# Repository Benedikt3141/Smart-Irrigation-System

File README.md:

→ AI Preview

# Smart Irrigation System

The Smart Irrigation System is a battery-powered monitoring and control system for watering up to six individual plants.
Each plant is monitored by a capacitive soil moisture sensor connected to the main control unit.

The project currently focuses on the main monitoring and control unit. A separate watering unit is planned but not fully designed yet. Communication between both units is intended to use ESP-NOW.

## Project Overview

The system consists of two main parts:

### Main Monitoring and Control Unit

The main unit collects sensor data, displays current measurements on a TFT screen, logs data to an SD card and indicates the system status using an LED strip.

Each soil moisture sensor is connected individually using an audio jack connector.

### Watering Unit

The watering unit is planned as a separate module. It will receive commands from the main control unit via ESP-NOW and control the water flow using a solenoid valve.
The unit should also monitor the water tank level using an ultrasonic sensor.

This part of the system is still work in progress.

## Feature overview

###### Sensors (Inputs)

- **Soil mositure monitoring** for individual plants
- **Temperature**
- Humidity
- Air pressure
- Air Quality
- CO2 concentration
- Solar intensity
- 4 Buttons
- *Tank fill state sensor*

###### Other features and outputs

- **Battery powered**
- 2.4" TFT LCD Screen with resistive touch
- SD log with data saved as .csv
- LED-Strip status indicator
- magnetic valve for watering Control
- *web interface*
- *Push Emails when water is empty/error etc.*

## Repository Structure

This repository contains both the firmware and the PCB design files.

- `/firmware/` contains the PlatformIO firmware project.
- `/firmware/src/` contains the ESP32 source code.
- `/src/pcb/` contains the KiCad PCB design files.
- `/src/pcb/gerbers/` contains the exported Gerber files for manufacturing.

## File Structure

```
Smart-Irrigation-System/
├── firmware/
├── images/
├── src/│  
│   ├── assembly_and_models/
│   │   ├── SmartIrrigationSystem-Assembly.step
│   │   └── SmartIrrigationSystem.FCStd
│   └── pcb/
│       └── Smart_Irrigation_SytemV2/
├── .gitignore
├── BOM.csv
├── Concept.jpg
├── JOURNAL.md
├── LICENSE
├── README.md
├── cart_adafruit.png
└── cart_jlcpcb.png

```

## Getting started

#### Requirements

To work with this project, you need:

* VS Code
* PlatformIO or pioarduino IDE Extension
* C++ Compiler
* KiCad 10.0.1 or later

#### Installation

Use git to clone this repository into your computer.

```
git clone https://github.com/Benedikt3141/Smart-Irrigation-System.git
```

Open the project folder in VS Code and build/upload the firmware using PlatformIO or pioarduino.

###### Hardware

You can either use the provided Gerber files or modify the KiCad project and generate new manufacturing files for your preferred PCB supplier.

You can find the gerberfiles [here ](src/pcb/Smart_Irrigation_SystemV2/production). The correlating `BOM.csv` and `position.csv` can be found in the same directories.

## License

[MIT](https://choosealicense.com/licenses/mit/)

## Current Project Status

This project is still in development.

The main monitoring unit is mostly implemented. The watering unit, web interface and notification system are planned but not finished yet.

## Sources

[MQ2 Library](https://github.com/labay11/MQ-2-sensor-library/)
[SD Card](https://RandomNerdTutorials.com/esp32-web-server-microsd-card/)

## AI Usage

Most of the code was written by myself. Since this is a work in progress, the code may still contain bugs or parts that could be improved.

I used AI for debugging assistance, spelling correction, research and for generating the concept visualization shown at the top of this README.

The visualization is intended only as a preview of the planned device and
does not represent the final manufactured hardware.

The PCB design, hardware architecture and most of the firmware were
created by myself.

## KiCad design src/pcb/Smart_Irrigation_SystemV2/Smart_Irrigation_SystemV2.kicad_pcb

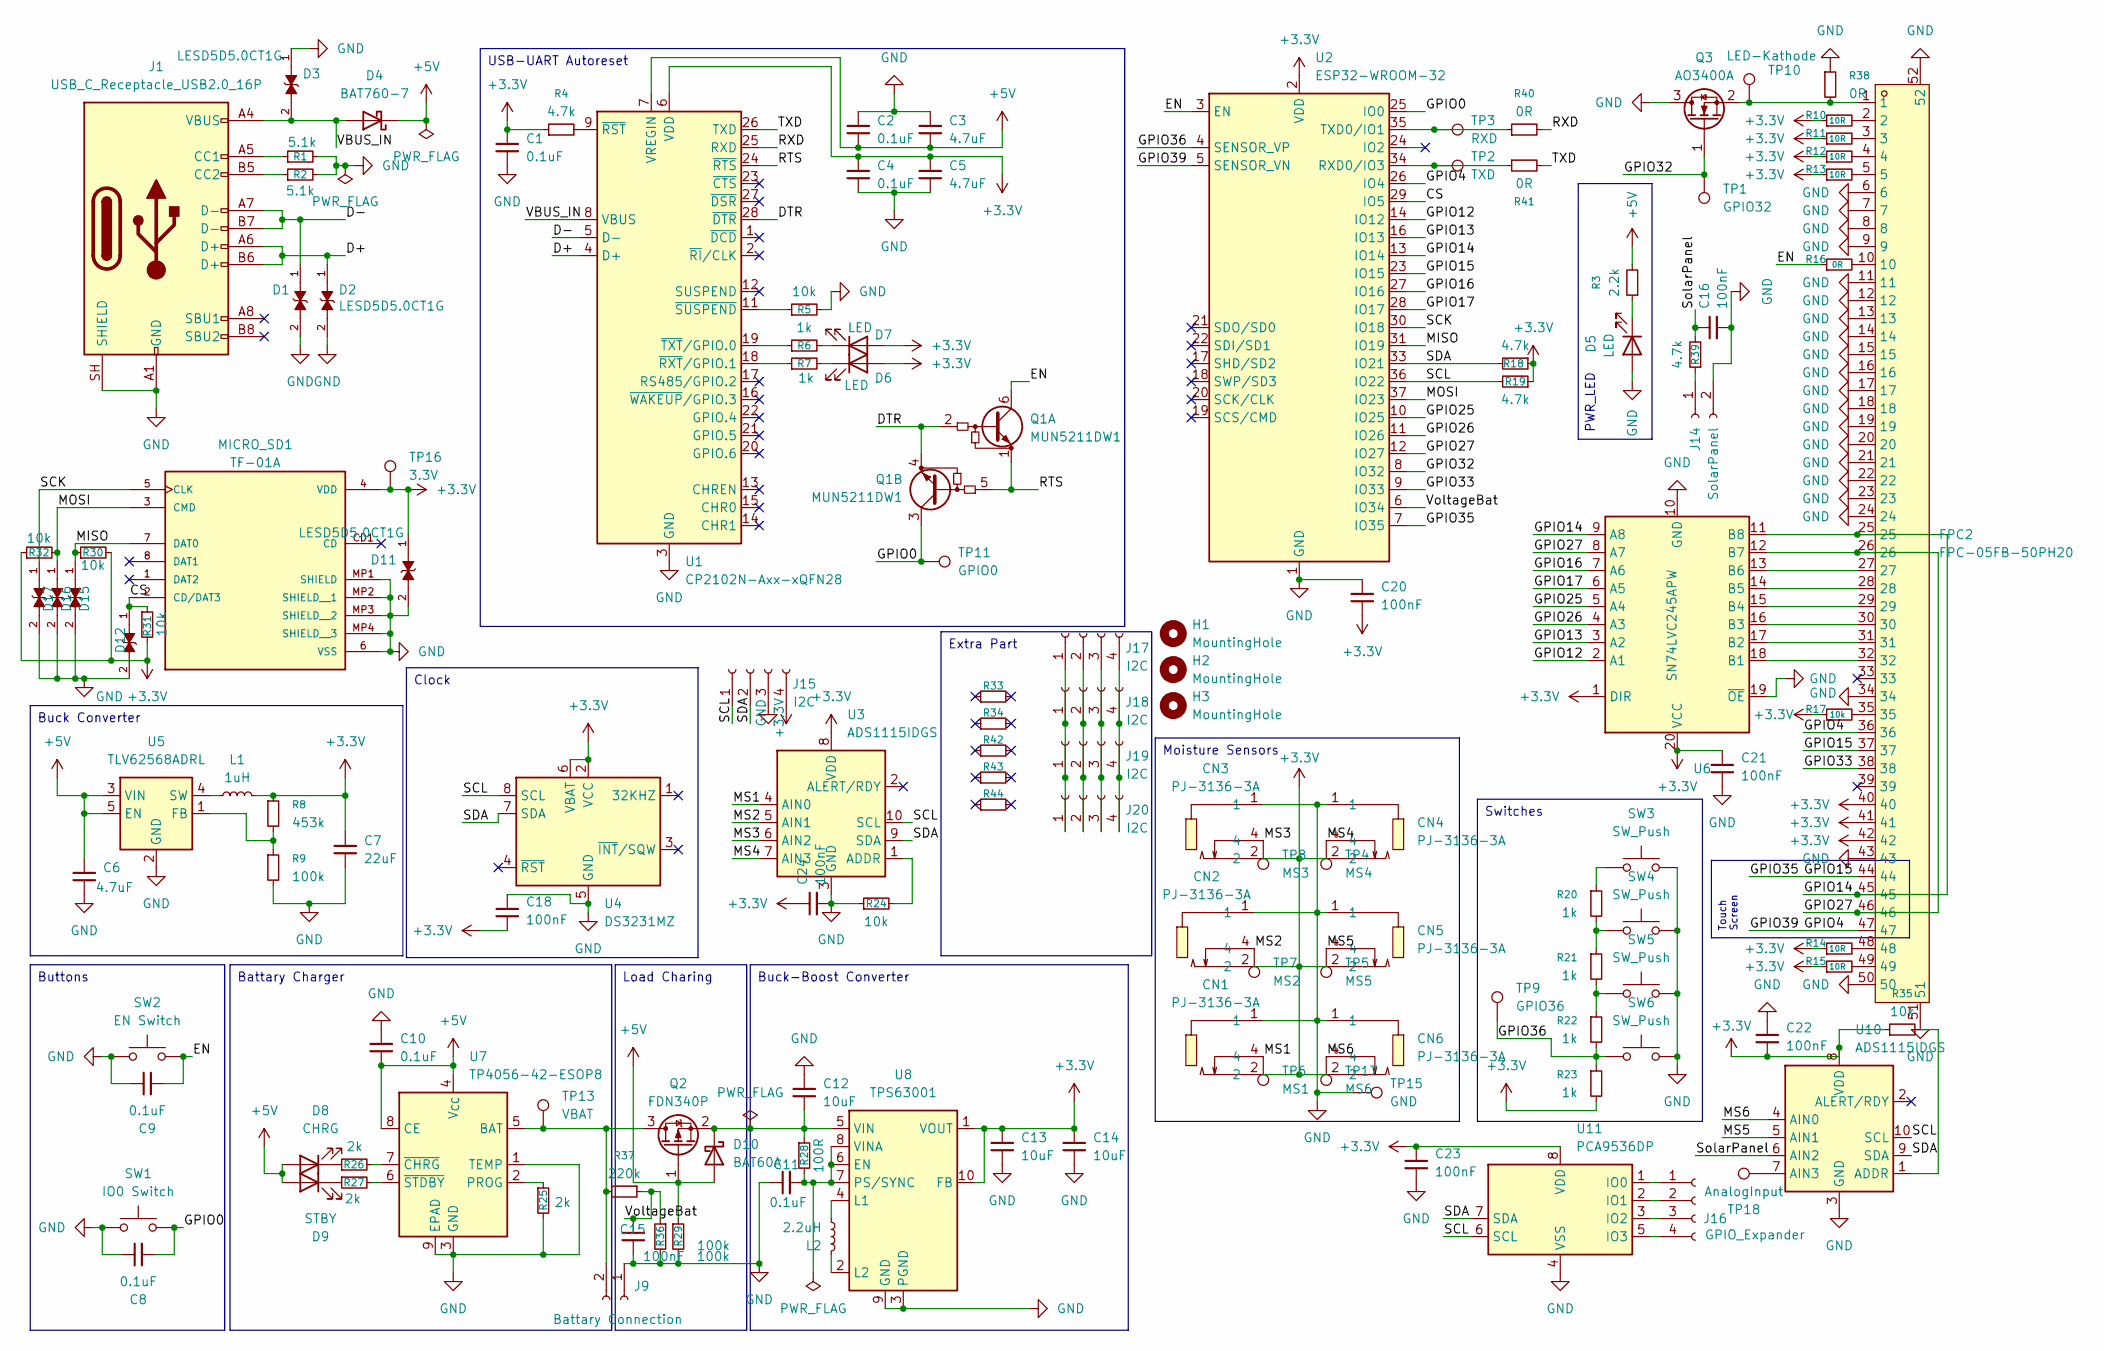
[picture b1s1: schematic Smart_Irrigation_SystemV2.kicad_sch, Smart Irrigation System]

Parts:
C1, C2, C4, C8, C9, C10, C11: 0.1uF; C_0805_2012Metric; JLCPCB Part Number C28233
C3, C5, C6: 4.7uF; C_0805_2012Metric; JLCPCB Part Number C1779
C7: 22uF; C_0805_2012Metric; JLCPCB Part Number C45783
C12, C13, C14: 10uF; C_0805_2012Metric; JLCPCB Part Number C15850
C15, C16, C18, C20, C21, C22, C23, C24: 100nF; C_0805_2012Metric; JLCPCB Part Number C29926
CN1, CN2, CN3, CN4, CN5, CN6: PJ-3136-3A; AUDIO-TH_PJ-3136-3A; MPN PJ-3136-3A; LCSC Part C707248
D1, D2, D3, D11, D12, D15, D16, D17: LESD5D5.0CT1G; TVS_LESD5D5.0CT1G; PARTREV O; JLCPCB Part Number C5274290
D4: BAT760-7; D_SOD-323F; JLCPCB Part Number C27636120
D5, D6, D7: LED; D_0603_1608Metric; JLCPCB Part Number C2286
D8: CHRG; D_0603_1608Metric; JLCPCB Part Number C2287
D9: STBY; D_0603_1608Metric; JLCPCB Part Number C12624
D10: BAT60A; D_SOD-323; JLCPCB Part Number C513277
FPC2: FPC-05FB-50PH20; FPC-SMD_50P-P0.50_FPC-05FB-50PH20; MPN FPC-05FB-50PH20; LCSC Part C2856838
H1, H2, H3: MountingHole; MountingHole_2.2mm_M2
J1: USB_C_Receptacle_USB2.0_16P; USB_C_Receptacle_HCTL_HC-TYPE-C-16P-01A; JLCPCB Part Number C5337088
J9: Battary Connection; JST_PH_B2B-PH-K_1x02_P2.00mm_Vertical
J14: SolarPanel; JST_PH_B2B-PH-K_1x02_P2.00mm_Vertical
J15, J17, J18, J19, J20: I2C; PinSocket_1x04_P2.54mm_Vertical
J16: GPIO_Expander; PinSocket_1x04_P2.54mm_Vertical
L1: 1uH; IND-SMD_L7.1-W6.6; JLCPCB Part Number C726315
L2: 2.2uH; IND-SMD_L6.6-W6.6; JLCPCB Part Number C128686
MICRO_SD1: TF-01A; TF-SMD_TF-01A; JLCPCB Part Number C91145
Q1: MUN5211DW1; SOT-363_SC-70-6; JLCPCB Part Number C152507
Q2: FDN340P; SOT-23; JLCPCB Part Number C347510
Q3: AO3400A; SOT-23; JLCPCB Part Number C20917
R1, R2: 5.1k; R_0805_2012Metric; JLCPCB Part Number C26023
R3: 2.2k; R_0805_2012Metric; JLCPCB Part Number C17520
R4, R18, R19, R39: 4.7k; R_0805_2012Metric; JLCPCB Part Number C17673
R5, R17, R24, R30, R31, R32, R35: 10k; R_0805_2012Metric; JLCPCB Part Number C17414
R6, R7, R20, R21, R22, R23: 1k; R_0805_2012Metric; JLCPCB Part Number C17513
R8: 453k; R_0805_2012Metric; JLCPCB Part Number C17702
R9, R29, R36: 100k; R_0805_2012Metric; JLCPCB Part Number C25611
R10, R11, R12, R13, R14, R15: 10R; R_0805_2012Metric; JLCPCB Part Number C17415
R16: 0R; R_0805_2012Metric; JLCPCB Part Number C17477
R25, R26, R27: 2k; R_0805_2012Metric; JLCPCB Part Number C17604
R28: 100R; R_0805_2012Metric; JLCPCB Part Number C17408
R33: 0201; R_0201_0603Metric
R34: 0402; R_0402_1005Metric
R37: 220k; R_0805_2012Metric; JLCPCB Part Number C17556
R38: 0R; R_0805_2012Metric
R40, R41: 0R; R_1206_3216Metric; JLCPCB Part Number C17888
R42: 0603; R_0603_1608Metric
R43: 0805; R_0805_2012Metric
R44: 1206; R_1206_3216Metric
SW1: IO0 Switch; KEY-SMD_4P-L6.0-W6.0-P3.90-LS9.0; JLCPCB Part Number C83206
SW2: EN Switch; KEY-SMD_4P-L6.0-W6.0-P3.90-LS9.0; JLCPCB Part Number C83206
SW3, SW4, SW5, SW6: SW_Push; SW_PUSH_6mm_H5mm; JLCPCB Part Number C83206
TP1: GPIO32; TestPoint_Pad_D1.5mm
TP2: TXD; TestPoint_Pad_D1.5mm
TP3: RXD; TestPoint_Pad_D1.5mm
TP4: MS4; TestPoint_Pad_D1.5mm
TP5: MS5; TestPoint_Pad_D1.5mm
TP6: MS1; TestPoint_Pad_D1.5mm
TP7: MS2; TestPoint_Pad_D1.5mm
TP8: MS3; TestPoint_Pad_D1.5mm
TP9: GPIO36; TestPoint_Pad_D1.5mm
TP10: LED-Kathode; TestPoint_Pad_D1.5mm
TP11: GPIO0; TestPoint_Pad_D1.5mm
TP13: VBAT; TestPoint_Pad_D1.5mm
TP15: GND; TestPoint_Pad_2.5x2.5mm
TP16: 3.3V; TestPoint_Pad_2.5x2.5mm
TP17: MS6; TestPoint_Pad_D1.5mm
TP18: AnalogInput; TestPoint_Pad_D1.5mm
U1: CP2102N-Axx-xQFN28; QFN-28-1EP_5x5mm_P0.5mm_EP3.35x3.35mm; JLCPCB Part Number C964632
U2: ESP32-WROOM-32; JLCPCB Part Number C701343
U3, U10: ADS1115IDGS; TSSOP-10_3x3mm_P0.5mm; JLCPCB Part Number C37593
U4: DS3231MZ; SOIC-8_3.9x4.9mm_P1.27mm; JLCPCB Part Number C107410
U5: TLV62568ADRL; SOT-23-5; JLCPCB Part Number C87122
U6: SN74LVC245APW; TSSOP-20_4.4x6.5mm_P0.65mm; JLCPCB Part Number C7848
U7: TP4056-42-ESOP8; ESOP-8_L4.9-W3.9-P1.27-LS6.0-BL-EP; JLCPCB Part Number C16581
U8: TPS63001; VSON-10-1EP_3x3mm_P0.5mm_EP1.65x2.4mm_ThermalVias; JLCPCB Part Number C28060
U11: PCA9536DP; TSSOP-8_3x3mm_P0.65mm; JLCPCB Part Number C2649389

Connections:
+3.3V: C1.1, C4.1, C5.1, C7.1, C13.1, C14.1, C18.2, C20.2, C21.1, C22.2, C23.1, C24.1, CN1.2, CN2.2, CN3.2, CN4.2, CN5.2, CN6.2, D6.2 (A), D7.2 (A), D11.1, FPC2.40, FPC2.41, FPC2.42, J15.4, L1.2, MICRO_SD1.4 (VDD), R4.1, R8.1, R10.1, R11.1, R12.1, R13.1, R14.1, R15.1, R17.1, R18.1, R19.1, R23.2, R30.2, R31.2, R32.1, R35.1, TP16.1 (1_1), U1.6 (VDD), U2.2 (VDD), U3.8 (VDD), U4.2 (VCC), U4.6 (VBAT), U6.1 (DIR), U6.20 (VCC), U8.1 (VOUT), U8.10 (FB), U10.8 (VDD), U11.8 (VDD)
+5V: C2.2, C3.2, C6.1, C10.2, D4.1 (K), D8.2 (A), D9.2 (A), D10.2 (A), Q2.1 (G), R3.2, R29.1, U1.7 (VREGIN), U5.3 (VIN), U5.5 (EN), U7.4 (V_{CC}), U7.8 (CE)
/CS: D12.1, MICRO_SD1.2 (CD/DAT3), R31.1, U2.29 (IO5)
/D+: D2.1, J1.A6 (D+), J1.B6 (D+), U1.4 (D+)
/D-: D1.1, J1.A7 (D-), J1.B7 (D-), U1.5 (D-)
/DTR: Q1.2 (B1), Q1.4 (E2), U1.28 (~DTR)
/EN: C9.2, Q1.6 (C1), R16.1, SW2.2, U2.3 (EN)
/GPIO0: C8.2, Q1.3 (C2), SW1.2, TP11.1 (1_1), U2.25 (IO0)
/GPIO12: U2.14 (IO12), U6.2 (A1)
/GPIO13: U2.16 (IO13), U6.3 (A2)
/GPIO14: FPC2.25, FPC2.45, U2.13 (IO14), U6.9 (A8), U6.11 (B8)
/GPIO15: FPC2.37, FPC2.44, U2.7 (IO35), U2.23 (IO15)
/GPIO16: U2.27 (IO16), U6.7 (A6)
/GPIO17: U2.28 (IO17), U6.6 (A5)
/GPIO25: U2.10 (IO25), U6.5 (A4)
/GPIO26: U2.11 (IO26), U6.4 (A3)
/GPIO27: FPC2.26, FPC2.46, U2.12 (IO27), U6.8 (A7), U6.12 (B7)
/GPIO32: Q3.1 (G), TP1.1 (1_1), U2.8 (IO32)
/GPIO33: FPC2.38, U2.9 (IO33)
/GPIO36: R22.2, R23.1, SW6.1, TP9.1 (1_1), U2.4 (SENSOR_VP)
/GPIO39: FPC2.36, FPC2.47, U2.5 (SENSOR_VN), U2.26 (IO4)
/MISO: D15.1, MICRO_SD1.7 (DAT0), R30.1, U2.31 (IO19)
/MOSI: D16.1, MICRO_SD1.3 (CMD), R32.2, U2.37 (IO23)
/MS1: CN1.4, TP6.1 (1_1), U3.4 (AIN0)
/MS2: CN2.4, TP7.1 (1_1), U3.5 (AIN1)
/MS3: CN3.4, TP8.1 (1_1), U3.6 (AIN2)
/MS4: CN4.4, TP4.1 (1_1), U3.7 (AIN3)
/MS5: CN5.4, TP5.1 (1_1), U10.5 (AIN1)
/MS6: CN6.4, TP17.1 (1_1), U10.4 (AIN0)
/RTS: Q1.1 (E1), Q1.5 (B2), U1.24 (~RTS)
/RXD: R40.2, U1.25 (RXD)
/SCK: D17.1, MICRO_SD1.5 (CLK), U2.30 (IO18)
/SCL: J15.1, R19.2, U2.36 (IO22), U3.10 (SCL), U4.8 (SCL), U10.10 (SCL), U11.6 (SCL)
/SDA: J15.2, R18.2, U2.33 (IO21), U3.9 (SDA), U4.7 (SDA), U10.9 (SDA), U11.7 (SDA)
/SolarPanel: C16.1, R39.2, U10.6 (AIN2)
/TXD: R41.2, U1.26 (TXD)
/VBUS_IN: D3.2, D4.2 (A), J1.A4 (VBUS), J1.A9 (VBUS), J1.B4 (VBUS), J1.B9 (VBUS), U1.8 (VBUS)
/VoltageBat: C15.1, R36.1, R37.1, U2.6 (IO34)
GND: C1.2, C2.1, C3.1, C4.2, C5.2, C6.2, C7.2, C8.1, C9.1, C10.1, C11.1, C12.1, C13.2, C14.2, C15.2, C16.2, C18.1, C20.1, C21.2, C22.1, C23.2, C24.2, CN1.1, CN2.1, CN3.1, CN4.1, CN5.1, CN6.1, D1.2, D2.2, D3.1, D5.2 (A), D11.2, D12.2, D15.2, D16.2, D17.2, FPC2.6, FPC2.7, FPC2.8, FPC2.9, FPC2.11, FPC2.12, FPC2.13, FPC2.14, FPC2.15, FPC2.16, FPC2.17, FPC2.18, FPC2.19, FPC2.20, FPC2.21, FPC2.22, FPC2.23, FPC2.24, FPC2.34, FPC2.43, FPC2.50, FPC2.51, FPC2.52, J1.A1 (GND), J1.A12 (GND), J1.B1 (GND), J1.B12 (GND), J1.SH (SHIELD), J9.1, J14.2, J15.3, MICRO_SD1.6 (VSS), MICRO_SD1.MP1 (SHIELD), MICRO_SD1.MP2 (SHIELD__1), MICRO_SD1.MP3 (SHIELD__2), MICRO_SD1.MP4 (SHIELD__3), Q3.3 (D), R1.2, R2.2, R5.2, R9.2, R24.1, R25.2, R29.2, R36.2, R38.1, SW1.1, SW2.1, SW3.2, SW4.2, SW5.2, SW6.2, TP15.1 (1_1), U1.3 (GND), U1.29 (GND), U2.1 (GND), U2.15 (GND), U2.38 (GND), U2.39 (GND), U3.3 (GND), U4.5 (GND), U5.2 (GND), U6.10 (GND), U6.19 (~OE), U7.1 (TEMP), U7.3 (GND), U7.9 (EPAD), U8.3 (PGND), U8.9 (GND), U8.11 (PGND), U10.3 (GND), U11.4 (VSS)
unnamed: D5.1 (K), R3.1
unnamed: D6.1 (K), R7.2
unnamed: D7.1 (K), R6.2
unnamed: D8.1 (K), R26.1
unnamed: D9.1 (K), R27.1
unnamed: C12.2, D10.1 (K), Q2.2 (S), R28.1, U8.5 (VIN)
unnamed: FPC2.2, R10.2
unnamed: FPC2.3, R11.2
unnamed: FPC2.4, R12.2
unnamed: FPC2.5, R13.2
unnamed: FPC2.10, R16.2
unnamed: FPC2.35, R17.2
unnamed: FPC2.48, R14.2
unnamed: FPC2.49, R15.2
unnamed: J1.A5 (CC1), R1.1
unnamed: J1.B5 (CC2), R2.1
unnamed: J9.2, Q2.3 (D), R37.2, TP13.1 (1_1), U7.5 (BAT)
unnamed: J14.1, R39.1
unnamed: J16.1, U11.1 (IO0)
unnamed: J16.2, U11.2 (IO1)
unnamed: J16.3, U11.3 (IO2)
unnamed: J16.4, U11.5 (IO3)
unnamed: J17.1, J18.1, J19.1, J20.1
unnamed: J17.2, J18.2, J19.2, J20.2
unnamed: J17.3, J18.3, J19.3, J20.3
unnamed: J17.4, J18.4, J19.4, J20.4
unnamed: FPC2.1, Q3.2 (S), R38.2, TP10.1 (1_1)
unnamed: R20.1, SW3.1
unnamed: R20.2, R21.1, SW4.1
unnamed: R21.2, R22.1, SW5.1
unnamed: R4.2, U1.9 (~RST)
unnamed: R7.1, U1.18 (~RXT/GPIO.1)
unnamed: R5.1, U1.11 (~SUSPEND)
unnamed: R6.1, U1.19 (~TXT/GPIO.0)
unnamed: R41.1, TP2.1 (1_1), U2.34 (RXD0/IO3)
unnamed: R40.1, TP3.1 (1_1), U2.35 (TXD0/IO1)
unnamed: R24.2, U3.1 (ADDR)
unnamed: R8.2, R9.1, U5.1 (FB)
unnamed: L1.1, U5.4 (SW)
unnamed: FPC2.32, U6.18 (B1)
unnamed: FPC2.31, U6.17 (B2)
unnamed: FPC2.30, U6.16 (B3)
unnamed: FPC2.29, U6.15 (B4)
unnamed: FPC2.28, U6.14 (B5)
unnamed: FPC2.27, U6.13 (B6)
unnamed: R25.1, U7.2 (PROG)
unnamed: R26.2, U7.7 (~CHRG)
unnamed: R27.2, U7.6 (~STDBY)
unnamed: C11.2, R28.2, U8.6 (EN), U8.7 (PS/SYNC), U8.8 (VINA)
unnamed: L2.1, U8.4 (L1)
unnamed: L2.2, U8.2 (L2)
unnamed: R35.2, U10.1 (ADDR)
unnamed: TP18.1 (1_1), U10.7 (AIN3)

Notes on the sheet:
USB-UART Autoreset
Battary Charger
Clock
Buck Converter
PWR_LED
Buck-Boost Converter
Switches
Touch Screen
Buttons
Moisture Sensors
Load Charing
Extra Part

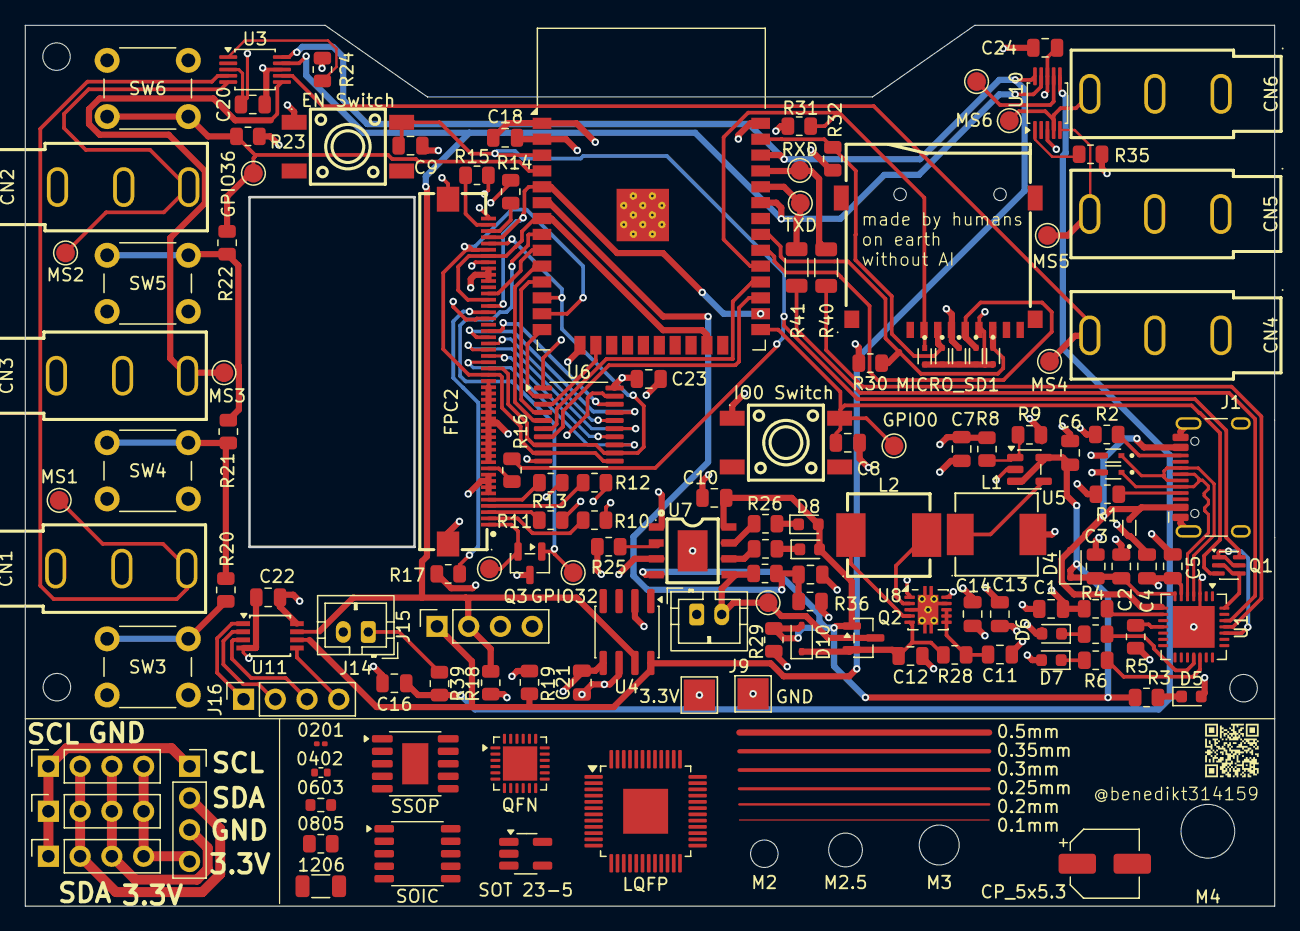
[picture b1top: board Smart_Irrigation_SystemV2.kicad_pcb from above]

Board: 4 copper layers, 100.0 x 70.5 mm, 137 parts (0 on the bottom side), 92 nets.

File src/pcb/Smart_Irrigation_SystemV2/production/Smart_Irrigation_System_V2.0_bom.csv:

Designator,Footprint,Quantity,Value,LCSC Part #
"C1, C10, C11, C2, C4, C8, C9",0805,7,0.1uF,C28233
"C12, C13, C14",0805,3,10uF,C15850
"C15, C16, C17, C18, C20, C21, C22, C23, C24",0805,9,100nF,C29926
"C3, C5, C6",0805,3,4.7uF,C1779
C7,0805,1,22uF,C45783
"CN1, CN2, CN3, CN4, CN5, CN6",AUDIO-TH_PJ-3136-3A,6,PJ-3136-3A,C707248
"D1, D11, D12, D15, D16, D17, D2, D3",TVS_LESD5D5.0CT1G,8,LESD5D5.0CT1G,C5274290
D10,D_SOD-323,1,BAT60A,C5355496
D4,D_SOD-323F,1,BAT760-7,C27636120
"D5, D6, D7",0603,3,LED,C2286
D8,0603,1,CHRG,C2287
D9,0603,1,STBY,C12624
J1,USB_C_Receptacle_HCTL_HC-TYPE-C-16P-01A,1,USB_C_Receptacle_USB2.0_16P,C5337088
"J10, J11, J13, J15, J6",JST_EH_B4B-EH-A_1x04_P2.50mm_Vertical,5,I2C,
J14,JST_PH_B2B-PH-K_1x02_P2.00mm_Vertical,1,SolarPanel,
J16,PinSocket_1x04_P2.54mm_Vertical,1,GPIO_Expander,
J2,CON_5051105091_MOL,1,FPC_Connector,C779387
J9,JST_PH_B2B-PH-K_1x02_P2.00mm_Vertical,1,Battary Connection,
L1,IND-SMD_L7.1-W6.6,1,1uH,C726315
L2,IND-SMD_L6.6-W6.6,1,2.2uH,C128686
MICRO_SD1,TF-SMD_TF-01A,1,TF-01A,C91145
Q1,SOT-363_SC-70-6,1,MUN5211DW1,C152507
Q2,SOT-23,1,FDN340P,C347510
Q3,SOT-23,1,AO3400A,C20917
"R1, R2",0805,2,5.1k,C26023
"R10, R11, R12, R13, R14, R15",0805,6,10R,C17415
R16,0805,1,0R,C17477
"R17, R24, R30, R31, R32, R35, R5",0805,7,10k,C17414
"R18, R19, R39, R4",0805,4,4.7k,C17673
"R20, R21, R22, R23, R6, R7",0805,6,1k,C17513
"R25, R26, R27",0805,3,2k,C17604
R28,0805,1,100R,C17408
"R29, R36, R9",0805,3,100k,C25611
R3,0805,1,2.2k,C17520
R37,0805,1,220k,C17556
"R40, R41",1206,2,0R,C17888
R8,0805,1,453k,C17702
SW1,KEY-SMD_4P-L6.0-W6.0-P3.90-LS9.0,1,IO0 Switch,C83206
SW2,KEY-SMD_4P-L6.0-W6.0-P3.90-LS9.0,1,EN Switch,C83206
"SW3, SW4, SW5, SW6",SW_PUSH_6mm_H4.3mm,4,SW_Push,
TP1,TestPoint_Pad_D1.5mm,1,GPIO32,
TP10,TestPoint_Pad_D1.5mm,1,LED-Kathode,
TP11,TestPoint_Pad_D1.5mm,1,GPIO0,
TP13,TestPoint_Pad_D1.5mm,1,VBAT,
TP14,TestPoint_Pad_D1.5mm,1,GND,
TP15,TestPoint_Pad_2.5x2.5mm,1,GND,
TP16,TestPoint_Pad_4.0x4.0mm,1,3.3V,
TP17,TestPoint_Pad_D1.5mm,1,MS6,
TP18,TestPoint_Pad_D1.5mm,1,AnalogInput,
TP2,TestPoint_Pad_D1.5mm,1,TXD,
TP3,TestPoint_Pad_D1.5mm,1,RXD,
TP4,TestPoint_Pad_D1.5mm,1,MS4,
TP5,TestPoint_Pad_D1.5mm,1,MS5,
TP6,TestPoint_Pad_D1.5mm,1,MS1,
TP7,TestPoint_Pad_D1.5mm,1,MS2,
TP8,TestPoint_Pad_D1.5mm,1,MS3,
TP9,TestPoint_Pad_D1.5mm,1,GPIO36,
U1,QFN-28-1EP_5x5mm_P0.5mm_EP3.35x3.35mm,1,CP2102N-Axx-xQFN28,C964632 
"U10, U3",TSSOP-10_3x3mm_P0.5mm,2,ADS1115IDGS,C37593
U11,TSSOP-8_3x3mm_P0.65mm,1,PCA9536DP,C2649389
U2,ESP32-WROOM-32,1,ESP32-WROOM-32,C701343
U4,SOIC-8_3.9x4.9mm_P1.27mm,1,DS3231MZ,C107410
U5,SOT-563,1,TLV62568ADRL,C87122
U6,TSSOP-20_4.4x6.5mm_P0.65mm,1,SN74LVC245APW,C7848
U7,ESOP-8_L4.9-W3.9-P1.27-LS6.0-BL-EP,1,TP4056-42-ESOP8,C16581
U8,VSON-10_L3.0-W3.0-P0.50-TL-EP_TPS62410DRCR,1,TPS63001,C28060
U9,SOIC-8_3.9x4.9mm_P1.27mm,1,AT24CS32-SSHM,C615972

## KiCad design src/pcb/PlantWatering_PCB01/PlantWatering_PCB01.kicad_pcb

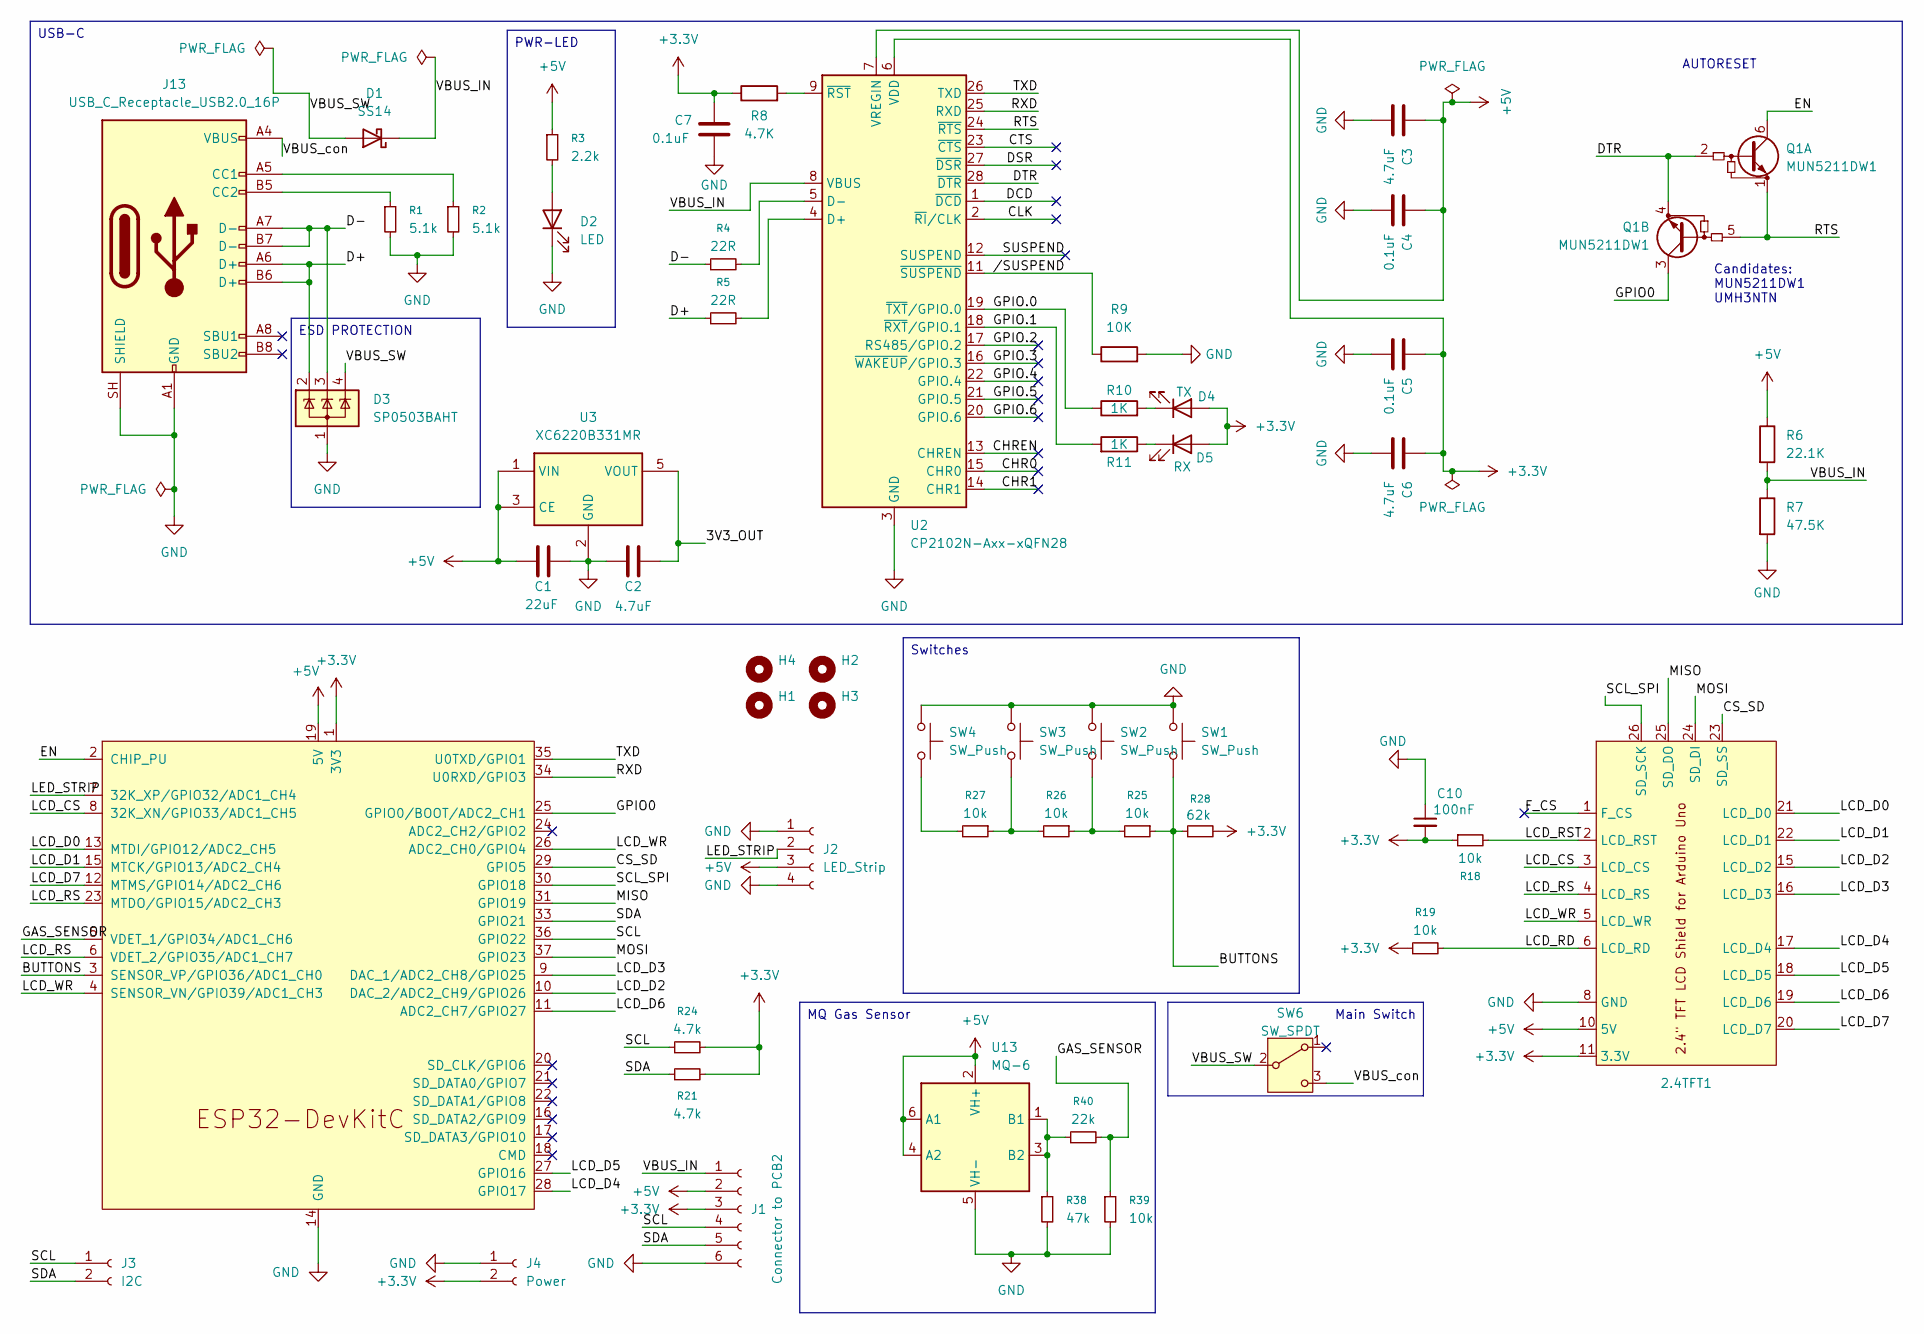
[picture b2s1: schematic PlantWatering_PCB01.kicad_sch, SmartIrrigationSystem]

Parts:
2.4TFT1: 2.4 TFT LCD Shield
C1: 22uF; C_1206_3216Metric; LCSC PN C5672
C2: 4.7uF; C_0805_2012Metric; LCSC PN C1779
C3, C6: 4.7uF; C_0805_2012Metric; Mouser PN GRM21BR71C475KE51L
C4, C5, C7: 0.1uF; C_0805_2012Metric; Mouser PN C0805C104K5RAC7411
C10: 100nF; C_0805_2012Metric; LCSC PN C28233
D1: SS14; D_SMA; LCSC PN C2480
D2: LED; LED_0603_1608Metric; LCSC PN C2286
D3: SP0503BAHT; SOT-143; LCSC PN C2682275
D4: TX; LED_0603_1608Metric; Mouser PN LTST-C170GKT
D5: RX; LED_0603_1608Metric; Mouser PN LTST-C170KFKT
H1, H2, H3, H4: MountingHole; MountingHole_3.2mm_M3
J1: Connector to PCB2; PinSocket_1x06_P2.00mm_Vertical
J2: LED_Strip; JST_PH_B4B-PH-K_1x04_P2.00mm_Vertical
J3: I2C; PinSocket_1x02_P2.00mm_Vertical
J4: Power; PinSocket_1x02_P2.00mm_Vertical
J13: USB_C_Receptacle_USB2.0_16P; USB_C_Receptacle_HRO_TYPE-C-31-M-12; LCSC PN C5337088
Q1: MUN5211DW1; SOT-363_SC-70-6; LCSC PN C152507
R1, R2: 5.1k; R_0805_2012Metric; LCSC PN C27834
R3: 2.2k; R_0805_2012Metric; LCSC PN C17520
R4, R5: 22R; R_0805_2012Metric; LCSC PN C17561
R6: 22.1K; R_0805_2012Metric; Mouser PN AC0805FR-0722K1L
R7: 47.5K; R_0805_2012Metric; Mouser PN AC0805FR-7W47K5L
R8: 4.7K; R_0805_2012Metric; Mouser PN AC0805FR-074K7L
R9: 10K; R_0805_2012Metric; Mouser PN AC0805FR-7W10KL
R10, R11: 1K; R_1206_3216Metric; Mouser PN AC0805FR-071KL
R18, R19, R25, R26, R27, R39: 10k; R_0805_2012Metric; LCSC PN C17414
R21, R24: 4.7k; R_0805_2012Metric; LCSC PN C17673
R28: 62k; R_0805_2012Metric; LCSC PN C17783
R38: 47k; R_0805_2012Metric; LCSC PN C17713
R40: 22k; R_0805_2012Metric; LCSC PN C17560
SW1, SW2, SW3, SW4: SW_Push; SW_PUSH_6mm
SW6: SW_SPDT; SW_CK_JS202011AQN_DPDT_Angled; LCSC PN C221662
U1: ESP32-DevKitC
U2: CP2102N-Axx-xQFN28; QFN-28-1EP_5x5mm_P0.5mm_EP3.35x3.35mm; LCSC PN C964632
U3: XC6220B331MR; SOT-23-5; LCSC PN C22466451
U13: MQ-6

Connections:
+3.3V: 2.4TFT1.11 (3.3V), C5.1, C6.1, C7.1, C10.2, D4.2 (A), D5.2 (A), J1.3, J4.2, R8.1, R18.1, R19.1, R21.2, R24.2, R28.2, U1.1 (3V3), U2.6 (VDD)
+5V: 2.4TFT1.10 (5V), C1.1, C3.1, C4.1, J1.2, J2.3, R3.1, R6.1, U1.19 (5V), U2.7 (VREGIN), U3.1 (VIN), U3.3 (CE), U13.2 (VH+), U13.4 (A2), U13.6 (A1)
/3V3_OUT: C2.2, U3.5 (VOUT)
/BUTTONS: R25.1, R28.1, SW1.2, U1.3 (SENSOR_VP/GPIO36/ADC1_CH0)
/CHR0: U2.15 (CHR0)
/CHR1: U2.14 (CHR1)
/CHREN: U2.13 (CHREN)
/CLK: U2.2 (~RI/CLK)
/CS_SD: 2.4TFT1.23 (SD_SS), U1.29 (GPIO5)
/CTS: U2.23 (~CTS)
/D+: D3.2 (K), J13.A6 (D+), J13.B6 (D+), R5.1
/D-: D3.3 (K), J13.A7 (D-), J13.B7 (D-), R4.1
/DCD: U2.1 (~DCD)
/DSR: U2.27 (~DSR)
/DTR: Q1.2 (B1), Q1.4 (E2), U2.28 (~DTR)
/EN: Q1.6 (C1), U1.2 (CHIP_PU)
/F_CS: 2.4TFT1.1 (F_CS)
/GAS_SENSOR: R39.1, R40.2, U1.5 (VDET_1/GPIO34/ADC1_CH6)
/GPIO0: Q1.3 (C2), U1.25 (GPIO0/BOOT/ADC2_CH1)
/GPIO.0: R10.1, U2.19 (~TXT/GPIO.0)
/GPIO.1: R11.2, U2.18 (~RXT/GPIO.1)
/GPIO.2: U2.17 (RS485/GPIO.2)
/GPIO.3: U2.16 (~WAKEUP/GPIO.3)
/GPIO.4: U2.22 (GPIO.4)
/GPIO.5: U2.21 (GPIO.5)
/GPIO.6: U2.20 (GPIO.6)
/LCD_CS: 2.4TFT1.3 (LCD_CS), U1.8 (32K_XN/GPIO33/ADC1_CH5)
/LCD_D0: 2.4TFT1.21 (LCD_D0), U1.13 (MTDI/GPIO12/ADC2_CH5)
/LCD_D1: 2.4TFT1.22 (LCD_D1), U1.15 (MTCK/GPIO13/ADC2_CH4)
/LCD_D2: 2.4TFT1.15 (LCD_D2), U1.10 (DAC_2/ADC2_CH9/GPIO26)
/LCD_D3: 2.4TFT1.16 (LCD_D3), U1.9 (DAC_1/ADC2_CH8/GPIO25)
/LCD_D4: 2.4TFT1.17 (LCD_D4), U1.28 (GPIO17)
/LCD_D5: 2.4TFT1.18 (LCD_D5), U1.27 (GPIO16)
/LCD_D6: 2.4TFT1.19 (LCD_D6), U1.11 (ADC2_CH7/GPIO27)
/LCD_D7: 2.4TFT1.20 (LCD_D7), U1.12 (MTMS/GPIO14/ADC2_CH6)
/LCD_RD: 2.4TFT1.6 (LCD_RD), R19.2
/LCD_RS: 2.4TFT1.4 (LCD_RS), U1.6 (VDET_2/GPIO35/ADC1_CH7), U1.23 (MTDO/GPIO15/ADC2_CH3)
/LCD_RST: 2.4TFT1.2 (LCD_RST), R18.2
/LCD_WR: 2.4TFT1.5 (LCD_WR), U1.4 (SENSOR_VN/GPIO39/ADC1_CH3), U1.26 (ADC2_CH0/GPIO4)
/LED_STRIP: J2.2, U1.7 (32K_XP/GPIO32/ADC1_CH4)
/MISO: 2.4TFT1.25 (SD_DO), U1.31 (GPIO19)
/MOSI: 2.4TFT1.24 (SD_DI), U1.37 (GPIO23)
/RTS: Q1.1 (E1), Q1.5 (B2), U2.24 (~RTS)
/RXD: U1.34 (U0RXD/GPIO3), U2.25 (RXD)
/SCL: J1.4, J3.1, R24.1, U1.36 (GPIO22)
/SCL_SPI: 2.4TFT1.26 (SD_SCK), U1.30 (GPIO18)
/SDA: J1.5, J3.2, R21.1, U1.33 (GPIO21)
/SUSPEND: U2.12 (SUSPEND)
/TXD: U1.35 (U0TXD/GPIO1), U2.26 (TXD)
/VBUS_IN: D1.1 (K), J1.1, R6.2, R7.1, U2.8 (VBUS)
/VBUS_SW: D1.2 (A), D3.4 (K), SW6.2 (B)
/VBUS_con: J13.A4 (VBUS), J13.A9 (VBUS), J13.B4 (VBUS), J13.B9 (VBUS), SW6.3 (C)
//SUSPEND: R9.1, U2.11 (~SUSPEND)
GND: 2.4TFT1.8 (GND), C1.2, C2.1, C3.2, C4.2, C5.2, C6.2, C7.2, C10.1, D2.1 (K), D3.1 (A), J1.6, J2.1, J2.4, J4.1, J13.A1 (GND), J13.A12 (GND), J13.B1 (GND), J13.B12 (GND), J13.SH (SHIELD), R1.2, R2.2, R7.2, R9.2, R38.2, R39.2, SW1.1, SW2.1, SW3.1, SW4.1, U1.14 (GND), U1.32 (GND), U1.38 (GND), U2.3 (GND), U2.29 (GND), U3.2 (GND), U13.5 (VH-)
unnamed: D2.2 (A), R3.2
unnamed: D4.1 (K), R10.2
unnamed: D5.1 (K), R11.1
unnamed: J13.A5 (CC1), R2.1
unnamed: J13.B5 (CC2), R1.1
unnamed: R25.2, R26.1, SW2.2
unnamed: R26.2, R27.1, SW3.2
unnamed: R27.2, SW4.2
unnamed: R5.2, U2.4 (D+)
unnamed: R4.2, U2.5 (D-)
unnamed: R8.2, U2.9 (~RST)
unnamed: R38.1, R40.1, U13.1 (B1), U13.3 (B2)

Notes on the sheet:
Candidates: MUN5211DW1 UMH3NTN
AUTORESET
Switches
USB-C
Main Switch
PWR-LED
MQ Gas Sensor
ESD PROTECTION

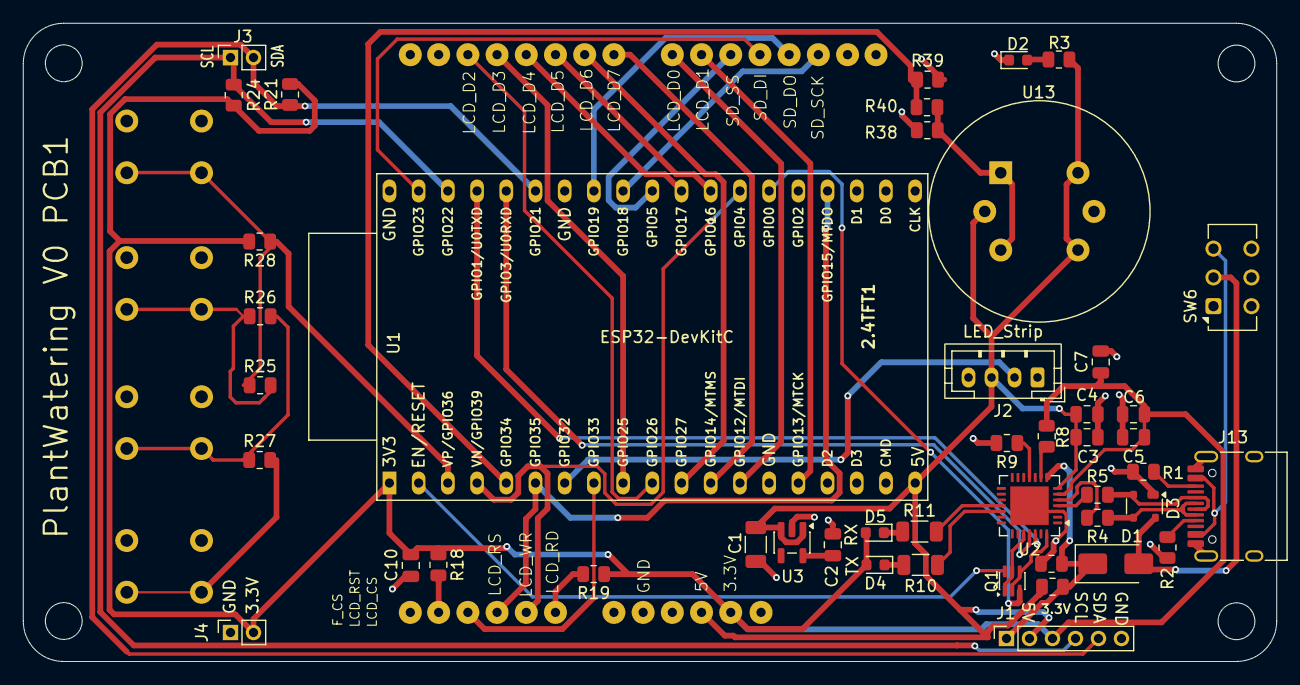
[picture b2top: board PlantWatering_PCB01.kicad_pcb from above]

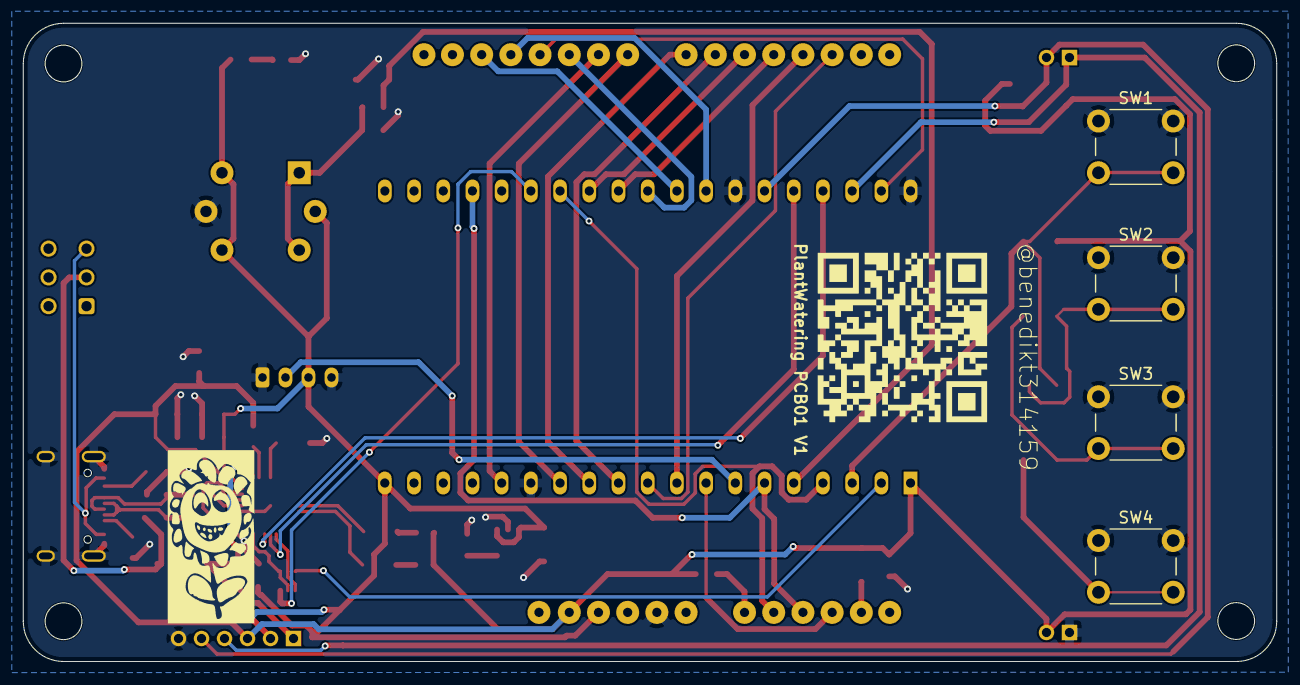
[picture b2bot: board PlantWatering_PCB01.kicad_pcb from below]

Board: 2 copper layers, 109.0 x 55.5 mm, 55 parts (4 on the bottom side), 52 nets.

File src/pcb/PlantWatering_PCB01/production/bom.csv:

Reference,Qty,Value,DNP,Exclude from BOM,Exclude from Board,Footprint,LCSC PN
C1,1,22uF,,,,Capacitor_SMD:C_1206_3216Metric,C5672
"C2,C3,C6",3,4.7uF,,,,Capacitor_SMD:C_0805_2012Metric,C1779
"C4,C5,C7",3,0.1uF,,,,Capacitor_SMD:C_0805_2012Metric,C28233
C10,1,100nF,,,,Capacitor_SMD:C_0805_2012Metric,C28233
D1,1,SS14,,,,Diode_SMD:D_SMA,C2480
D2,1,LED,,,,LED_SMD:LED_0603_1608Metric,C2286
D3,1,SP0503BAHT,,,,Package_TO_SOT_SMD:SOT-143,C2682275
D4,1,TX,,,,LED_SMD:LED_0603_1608Metric,C2286
D5,1,RX,,,,LED_SMD:LED_0603_1608Metric,C2286
J13,1,USB_C_Receptacle_USB2.0_16P,,,,Connector_USB:USB_C_Receptacle_HRO_TYPE-C-31-M-12,C5337088
Q1,1,MUN5211DW1,,,,Package_TO_SOT_SMD:SOT-363_SC-70-6,C152507
"R1,R2",2,5.1k,,,,Resistor_SMD:R_0805_2012Metric,C27834
R3,1,2.2k,,,,Resistor_SMD:R_0805_2012Metric,C17520
"R4,R5",2,22R,,,,Resistor_SMD:R_0805_2012Metric,C17561
R6,1,22.1K,,,,Resistor_SMD:R_0805_2012Metric,C17552
R7,1,47.5K,,,,Resistor_SMD:R_0805_2012Metric,C26011
R8,1,4.7K,,,,Resistor_SMD:R_0805_2012Metric,C17673
R9,1,10K,,,,Resistor_SMD:R_0805_2012Metric,C17414
"R10,R11",2,1K,,,,Resistor_SMD:R_1206_3216Metric,C1469
"R18,R19,R25,R26,R27,R39",6,10k,,,,Resistor_SMD:R_0805_2012Metric,C17414
"R21,R24",2,4.7k,,,,Resistor_SMD:R_0805_2012Metric,C17673
R28,1,62k,,,,Resistor_SMD:R_0805_2012Metric,C17783
R38,1,47k,,,,Resistor_SMD:R_0805_2012Metric,C17713
R40,1,22k,,,,Resistor_SMD:R_0805_2012Metric,C17560
SW6,1,SW_SPDT,,,,Button_Switch_THT:SW_CK_JS202011AQN_DPDT_Angled,C221662
U2,1,CP2102N-Axx-xQFN24,,,,Package_DFN_QFN:QFN-28-QFN-24-EP(4x4),C969151
U3,1,XC6220B331MR,,,,Package_TO_SOT_SMD:SOT-23-5,C22466451
